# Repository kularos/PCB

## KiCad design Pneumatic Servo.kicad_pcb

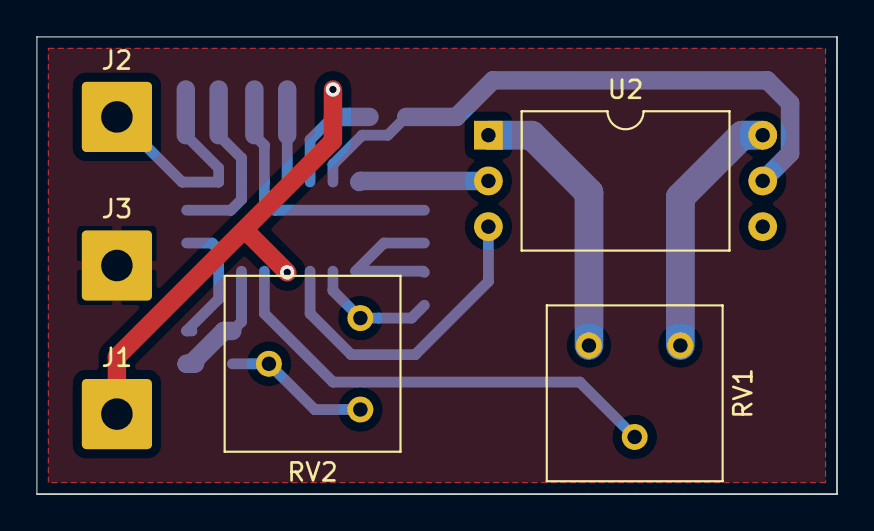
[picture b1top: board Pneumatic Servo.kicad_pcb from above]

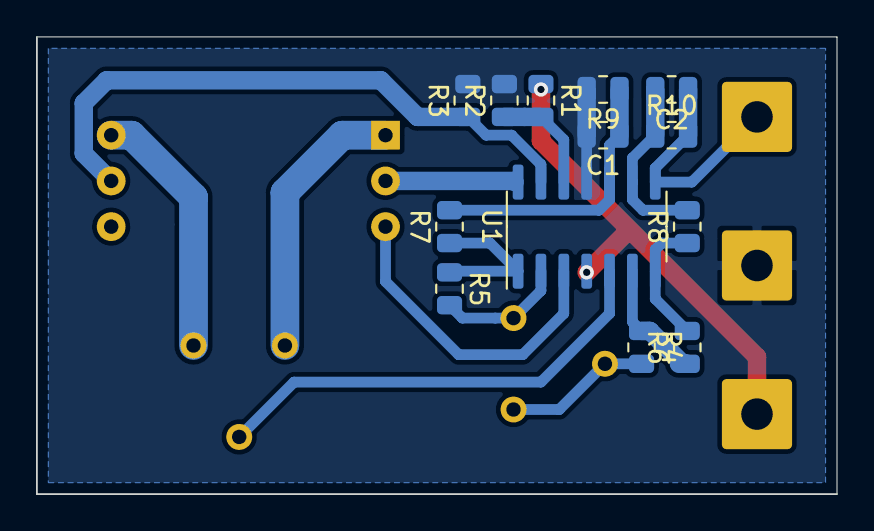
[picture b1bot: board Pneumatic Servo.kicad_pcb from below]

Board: 2 copper layers, 44.5 x 25.4 mm, 19 parts (13 on the bottom side), 17 nets.

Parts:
C1, C2: C; R_0805_2012Metric
J1, J2, J3: Conn_01x01_Male; SolderWire-1sqmm_1x01_D1.4mm_OD3.9mm
R1, R2, R3, R4, R5, R6, R7, R8, R9, R10: R; R_0805_2012Metric
RV1: TRIM; Potentiometer_Bourns_3386F_Vertical
RV2: GAIN; Potentiometer_Bourns_3386F_Vertical
U1: LM324; SOIC-14_3.9x8.7mm_P1.27mm
U2: FPN-07PG; DIP-6_W15.24mm

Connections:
+12V: J1.1, R1.1, U1.4
GND: C1.2, J3.1, R2.2, R3.2, R9.2, U1.11
unnamed: C1.1, R7.2, R9.1, U1.10
unnamed: C2.2, R8.2, R10.1, U1.9
unnamed: R1.2, R2.1, U1.12
unnamed: R3.1, U1.13, U2.5
unnamed: R4.1, R6.1, U1.6
unnamed: R4.2, RV2.2, RV2.3
unnamed: R5.1, R7.1, U1.1
unnamed: R5.2, RV2.1, U1.2
unnamed: R6.2, R8.1, U1.7
unnamed: RV1.1, U2.1
unnamed: RV1.2, U1.5
unnamed: RV1.3, U2.6
unnamed: U1.3, U2.3
unnamed: U1.14, U2.2
output: C2.1, J2.1, R10.2, U1.8
